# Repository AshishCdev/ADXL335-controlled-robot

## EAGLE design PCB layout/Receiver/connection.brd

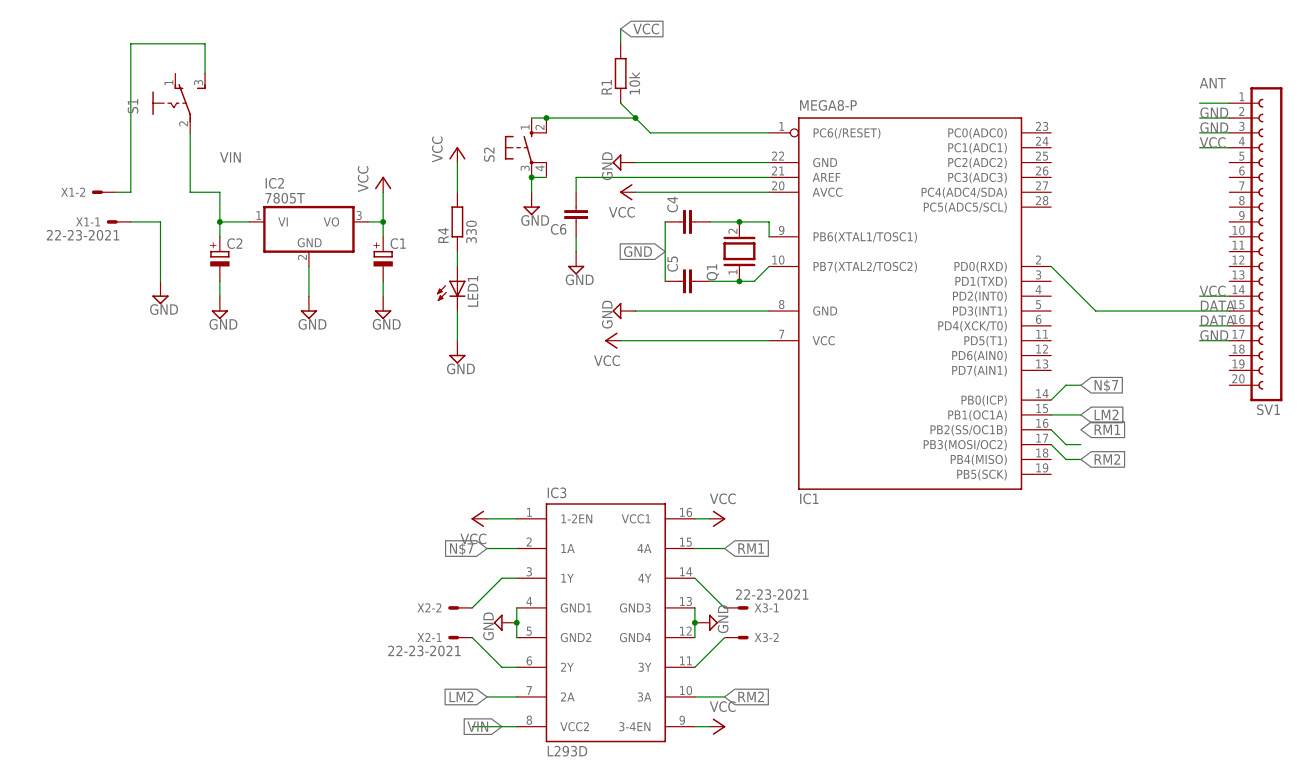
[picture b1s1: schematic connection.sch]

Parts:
C1, C2: CPOL-EUE3.5-8; E3,5-8
C4, C5, C6: C5/2.5; C5B2.5
IC1: MEGA8-P; DIL28-3
IC2: 7805T; TO220H
IC3: L293D; DIL16
LED1: LED5MM
Q1: XTAL/S; QS
R1: 10k; 0207/10
R4: 330; 0207/10
S1: 255SB
S2: 10-XX; B3F-10XX
SV1: FE20-1; FE20
X1, X2, X3: 22-23-2021

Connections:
ANT: SV1.1
DATA: IC1.2 (PD0(RXD)), SV1.15, SV1.16
GND: C1.-, C2.-, C4.1, C5.1, C6.1, IC1.8 (GND), IC1.22 (GND), IC2.2 (GND), IC3.4 (GND1), IC3.5 (GND2), IC3.12 (GND4), IC3.13 (GND3), LED1.K (C), S2.3, S2.4 (P1), SV1.2, SV1.3, SV1.17, X1.1
LM2: IC1.15 (PB1(OC1A)), IC3.7 (2A)
unnamed: IC1.1 (PC6(/RESET)), R1.1, S2.1 (S), S2.2 (S1)
unnamed: C6.2, IC1.21 (AREF)
unnamed: C4.2, IC1.9 (PB6(XTAL1/TOSC1)), Q1.2
unnamed: C5.2, IC1.10 (PB7(XTAL2/TOSC2)), Q1.1
unnamed: S1.3 (S), X1.2
unnamed: IC1.14 (PB0(ICP)), IC3.2 (1A)
unnamed: IC3.3 (1Y), X2.2
unnamed: IC3.6 (2Y), X2.1
unnamed: IC3.14 (4Y), X3.1
unnamed: IC3.11 (3Y), X3.2
unnamed: LED1.A, R4.1
RM1: IC1.16 (PB2(SS/OC1B)), IC3.15 (4A)
RM2: IC1.17 (PB3(MOSI/OC2)), IC3.10 (3A)
VCC: C1.+, IC1.7 (VCC), IC1.20 (AVCC), IC2.3 (VO), IC3.1 (1-2EN), IC3.9 (3-4EN), IC3.16 (VCC1), R1.2, R4.2, SV1.4, SV1.14
VIN: C2.+, IC2.1 (VI), IC3.8 (VCC2), S1.2

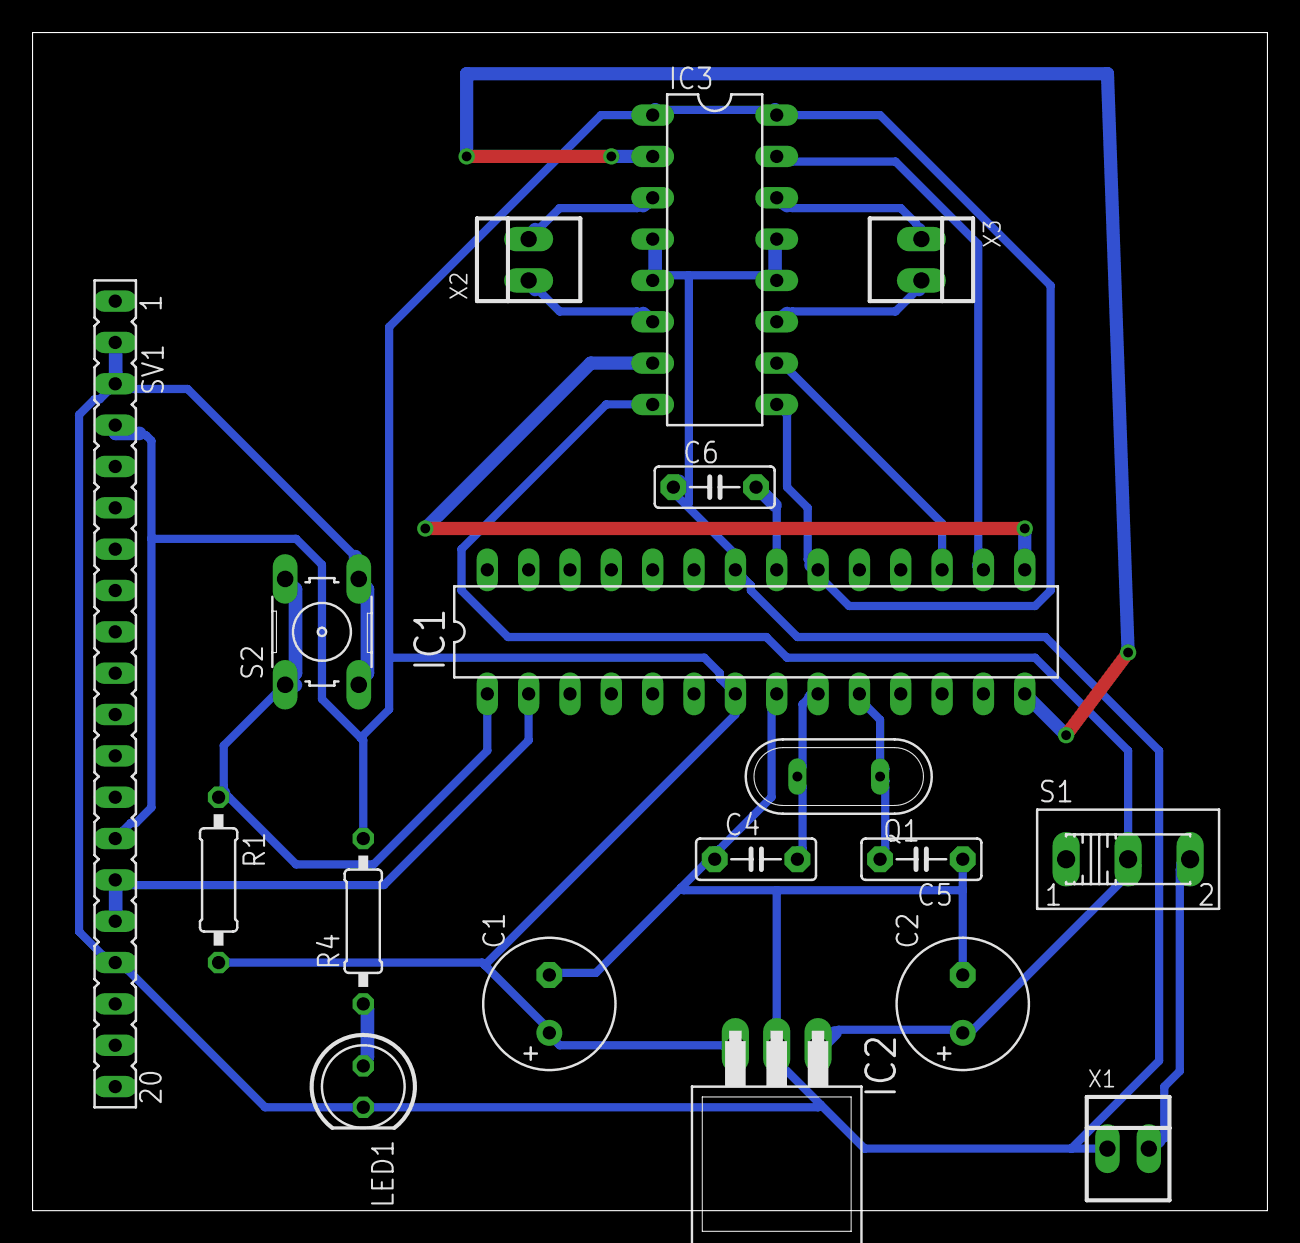
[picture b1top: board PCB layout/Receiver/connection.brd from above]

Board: 2 copper layers, 75.9 x 72.4 mm, 18 parts (0 on the bottom side), 18 nets.

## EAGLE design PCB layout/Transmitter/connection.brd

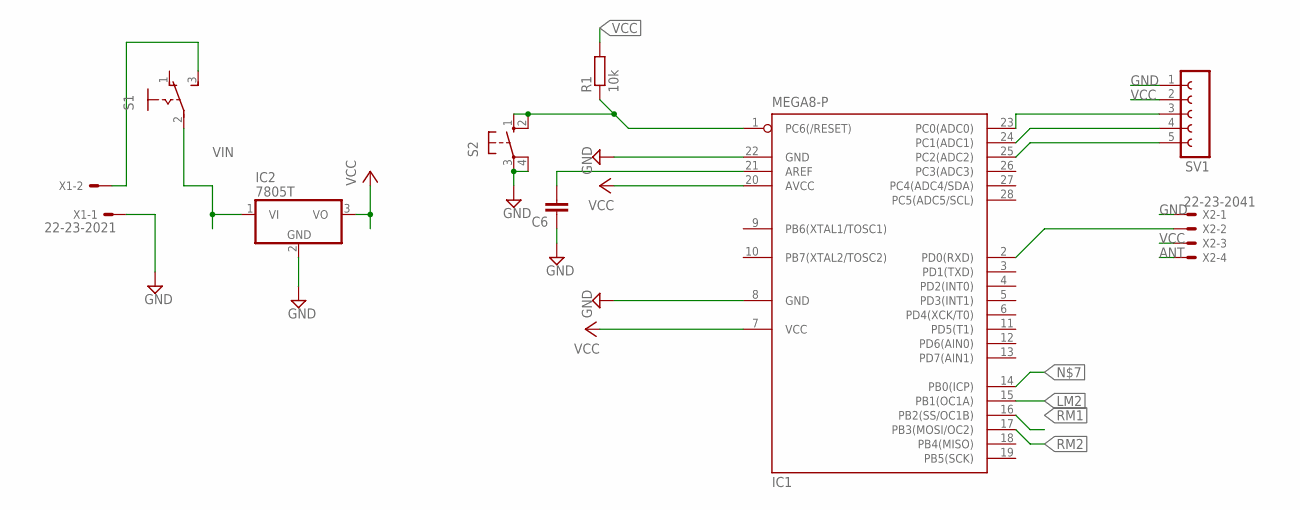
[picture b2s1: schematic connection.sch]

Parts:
C6: C5/2.5; C5B2.5
IC1: MEGA8-P; DIL28-3
IC2: 7805T; TO220H
R1: 10k; 0207/10
S1: 255SB
S2: 10-XX; B3F-10XX
SV1: FE05W
X1: 22-23-2021
X2: 22-23-2041

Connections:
ANT: X2.4
GND: C6.1, IC1.8 (GND), IC1.22 (GND), IC2.2 (GND), S2.3, S2.4 (P1), SV1.1, X1.1, X2.1
LM2: IC1.15 (PB1(OC1A))
unnamed: IC1.1 (PC6(/RESET)), R1.1, S2.1 (S), S2.2 (S1)
unnamed: C6.2, IC1.21 (AREF)
unnamed: S1.3 (S), X1.2
unnamed: IC1.23 (PC0(ADC0)), SV1.3
unnamed: IC1.24 (PC1(ADC1)), SV1.4
unnamed: IC1.25 (PC2(ADC2)), SV1.5
unnamed: IC1.2 (PD0(RXD)), X2.2
RM1: IC1.16 (PB2(SS/OC1B))
RM2: IC1.17 (PB3(MOSI/OC2))
VCC: IC1.7 (VCC), IC1.20 (AVCC), IC2.3 (VO), R1.2, SV1.2, X2.3
VIN: IC2.1 (VI), S1.2

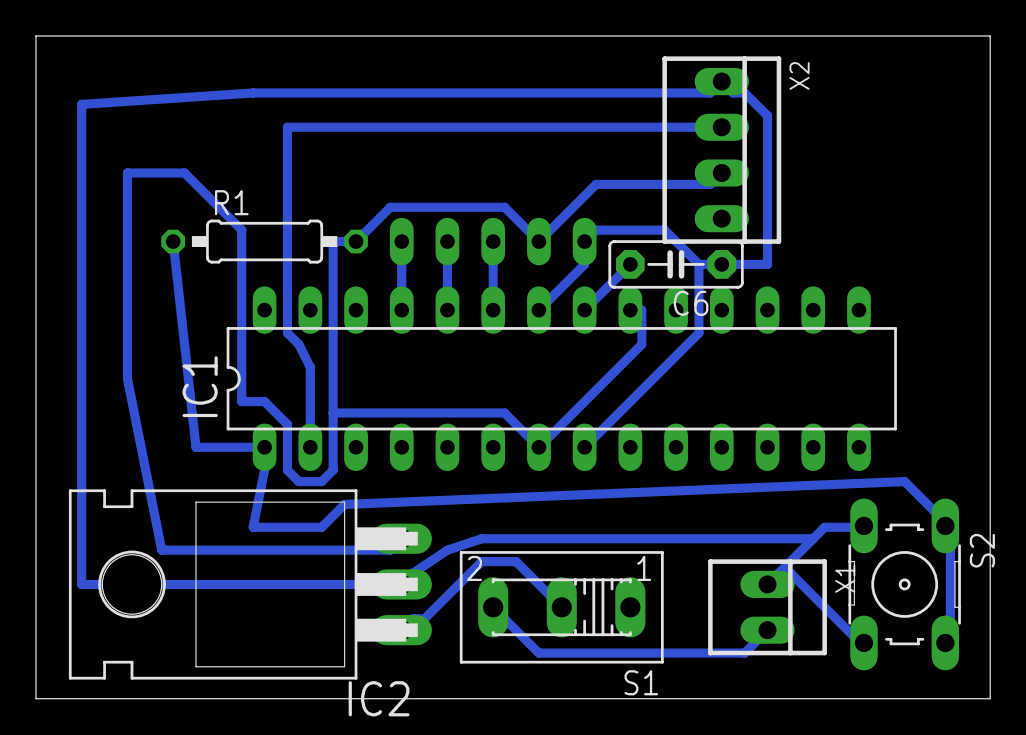
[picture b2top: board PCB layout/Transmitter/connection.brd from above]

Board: 2 copper layers, 53.0 x 36.8 mm, 9 parts (1 on the bottom side), 10 nets.

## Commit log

2016-01-07 added eagle layout
